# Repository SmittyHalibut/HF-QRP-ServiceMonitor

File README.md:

# HF-QRP-ServiceMonitor
A set of testing gear for your HF QRP radios.

* Documentation: https://docs.google.com/document/d/1AvHzDoBxXDUolqx6FsBMn076Gl0RjaEZqFqrANyeqWs/edit#
* YouTube Playlist of live streams where I did this work: https://www.youtube.com/watch?v=ZD_V13OpfFE&list=PLyhRhuo30TzVZJrvRoCTQwFVjwLlRqt9Y

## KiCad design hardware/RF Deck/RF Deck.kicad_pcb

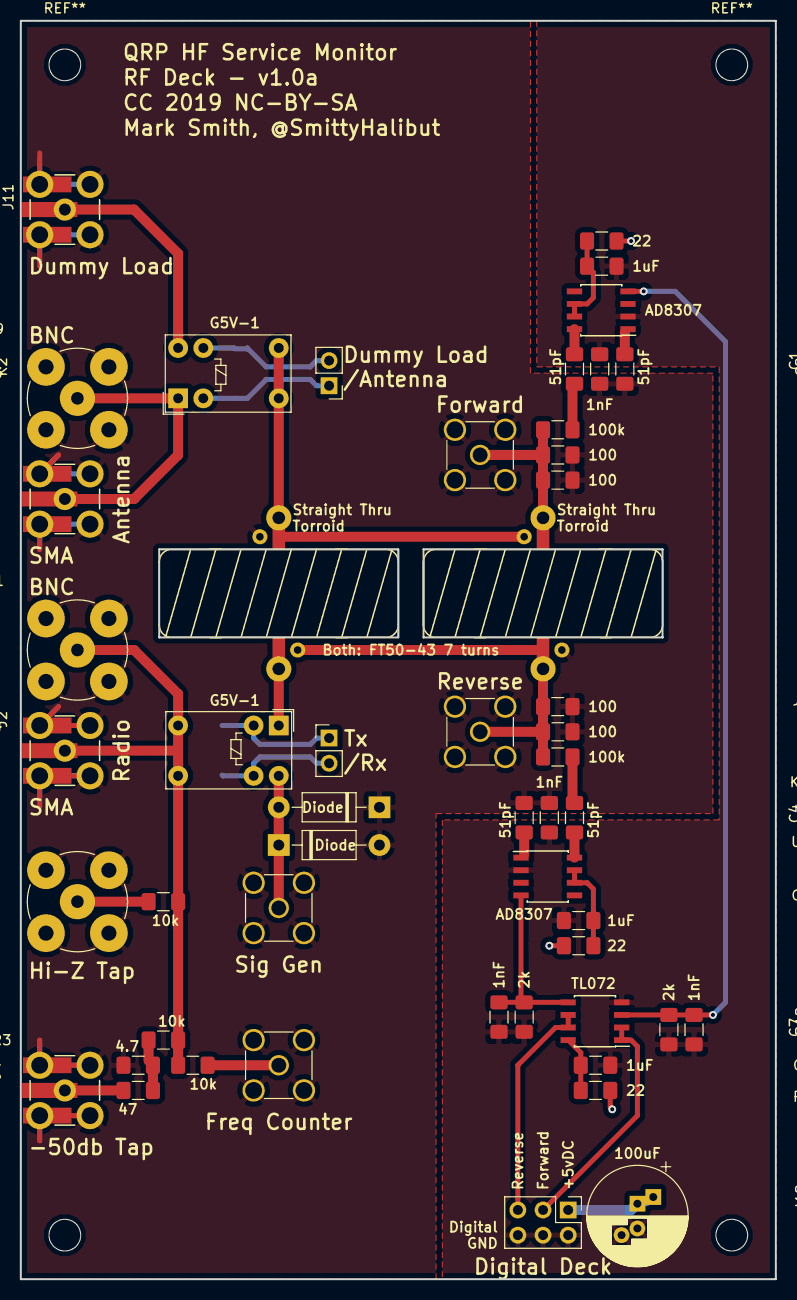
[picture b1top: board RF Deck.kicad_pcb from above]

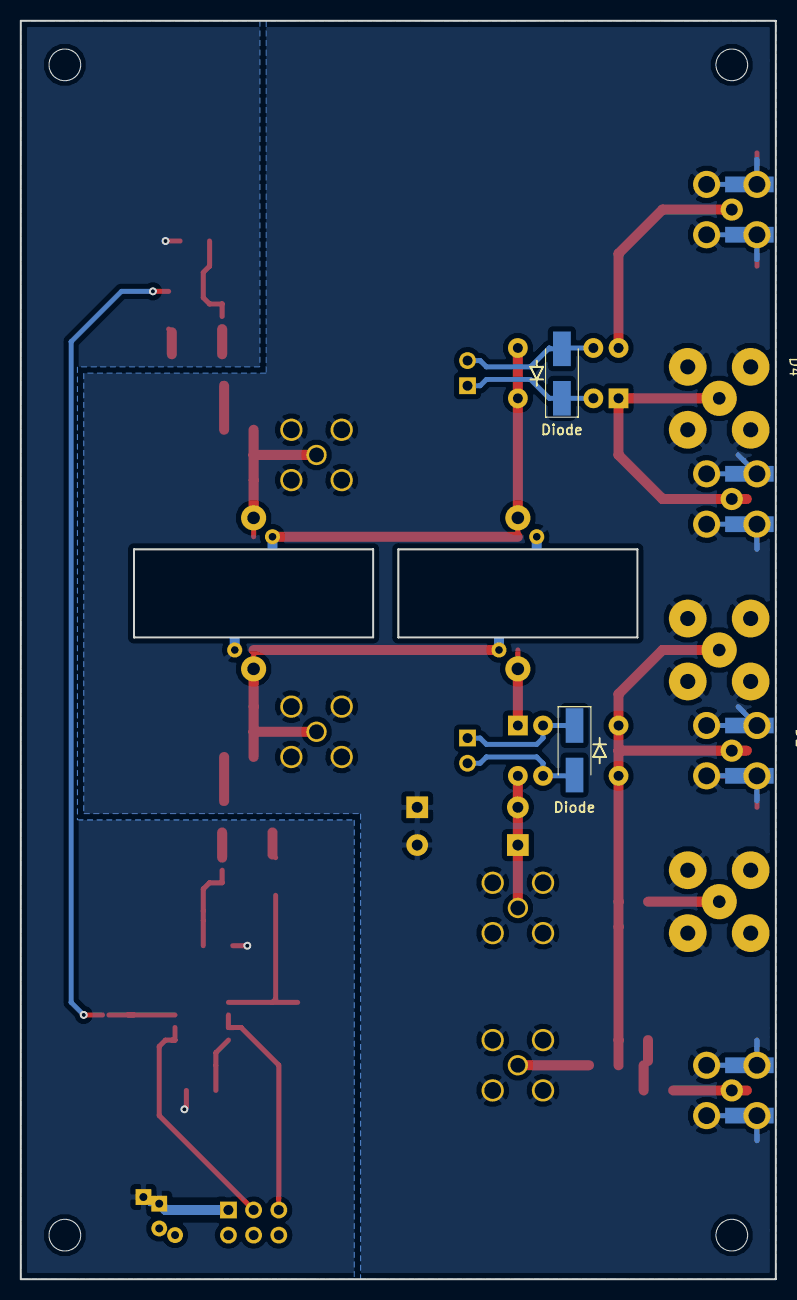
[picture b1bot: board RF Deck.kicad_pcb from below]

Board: 2 copper layers, 76.2 x 127.0 mm, 53 parts (2 on the bottom side), 32 nets.

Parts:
C1, C2, C4, C5: 51pF; C_1206_3216Metric_Pad1.42x1.75mm_HandSolder
C3, C7, C9, C12: 1nF; C_1206_3216Metric_Pad1.42x1.75mm_HandSolder
C6, C8, C11: .1uF; C_1206_3216Metric_Pad1.42x1.75mm_HandSolder
C10: 100uF; CP_Radial_D10.0mm_P2.50mm_P5.00mm
D1, D4: D_Small; D_SMA_Handsoldering
D2, D3: D_Small; D_DO-41_SOD81_P10.16mm_Horizontal
J1: RadioBNC; BNC_TEConnectivity_1478204_Vertical
J2: RadioSMA; SMA_Vertical_Or_Edge
J3: High Impedance Tap; BNC_TEConnectivity_1478204_Vertical
J4: Low Impedance Tap; SMA_Vertical_Or_Edge
J5: Frequency Counter; SMA_Amphenol_901-144_Vertical
J6: Signal Generator; SMA_Amphenol_901-144_Vertical
J7: Forward Sample; SMA_Amphenol_901-144_Vertical
J8: Reverse Sample; SMA_Amphenol_901-144_Vertical
J9: AntennaBNC; BNC_TEConnectivity_1478204_Vertical
J10: AntennaSMA; SMA_Vertical_Or_Edge
J11: Dummy Load; SMA_Vertical_Or_Edge
J12: To Digital Deck; PinHeader_2x03_P2.54mm_Vertical
J13: Ant/Dummy; PinHeader_1x02_P2.54mm_Vertical
J14: Tx/Rx; PinHeader_1x02_P2.54mm_Vertical
K1, K2: G5V-1; Relay_SPDT_Omron_G5V-1
R1, R3, R5: 10k; R_1206_3216Metric_Pad1.42x1.75mm_HandSolder
R2: 47; R_1206_3216Metric_Pad1.42x1.75mm_HandSolder
R4: 4.7; R_1206_3216Metric_Pad1.42x1.75mm_HandSolder
R6, R7, R8, R9: 100; R_1206_3216Metric_Pad1.42x1.75mm_HandSolder
R10, R11: 100k?; R_1206_3216Metric_Pad1.42x1.75mm_HandSolder
R12, R13: 2k; R_1206_3216Metric_Pad1.42x1.75mm_HandSolder
R14, R15, R16: 22; R_1206_3216Metric_Pad1.42x1.75mm_HandSolder
T1, T2: Toroidal_Transformer; Toroid-FT50-43-In-Board
U1, U2: AD8307; SOIC-8_3.9x4.9mm_P1.27mm
U3: TL072; SOIC-8_3.9x4.9mm_P1.27mm

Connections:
+5V: C10.1, J12.1, R14.1, R15.1, R16.1
ForwardPwr: J12.3, U3.1, U3.2
GNDD: C3.1, C6.1, C7.1, C8.1, C9.1, C10.2, C11.1, C12.1, J12.2, J12.4, J12.6, R12.1, R13.1, U1.2, U2.2, U3.4
GNDS: C2.2, C3.2, C5.2, C12.2, D2.2, D3.1, J1.2, J2.2, J3.2, J4.2, J5.2, J6.2, J7.2, J8.2, J9.2, J10.2, J11.2, R4.1, R6.2, R7.2, R8.2, R9.2, T1.4, T2.3
unnamed: C1.1, U1.8
unnamed: C1.2, R10.1
unnamed: C2.1, U1.1
unnamed: C4.1, U2.8
unnamed: C4.2, R11.1
unnamed: C5.1, U2.1
unnamed: C6.2, R14.2, U1.6, U1.7
unnamed: C7.2, R12.2, U1.4, U3.3
unnamed: C8.2, R15.2, U2.6, U2.7
unnamed: C9.2, R13.2, U2.4, U3.5
unnamed: C11.2, R16.2, U3.8
unnamed: D1.1, J14.1, K1.2
unnamed: D1.2, J14.2, K1.9
unnamed: D2.1, D3.2, J6.1, K1.10
unnamed: D4.1, J13.1, K2.2
unnamed: D4.2, J13.2, K2.9
unnamed: J1.1, J2.1, K1.5, K1.6, R1.1, R3.1, R5.1
unnamed: J3.1, R1.2
unnamed: J4.1, R2.2
unnamed: J5.1, R3.2
unnamed: J7.1, R8.1, R9.1, R10.2, T2.2
unnamed: J8.1, R6.1, R7.1, R11.2, T1.3, T2.1
unnamed: J9.1, J10.1, K2.1
unnamed: J11.1, K2.10
unnamed: K1.1, T1.1
unnamed: K2.5, K2.6, T1.2, T2.4
unnamed: R2.1, R4.2, R5.2
ReversePwr: J12.5, U3.6, U3.7

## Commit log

2019-09-11 Initial commit. This is the result of Part 2 of my live stream: https://youtu.be/lJO46zwFvQI
2019-09-11 Added a (very) little bit to README.md
2019-11-02 Adding .gitignore to ingore gerbers, drills, and other derived files.
2019-11-02 Updated silkscreen and moved a few things around. AS ORDERED 2019-11-02
